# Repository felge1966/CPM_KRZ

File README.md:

# CPM_KRZ
Extrakt aus dem Beitrag im Robotrontrechnik-Forum

(https://www.robotrontechnik.de/html/forum/thwb/showtopic.php?threadid=12101)

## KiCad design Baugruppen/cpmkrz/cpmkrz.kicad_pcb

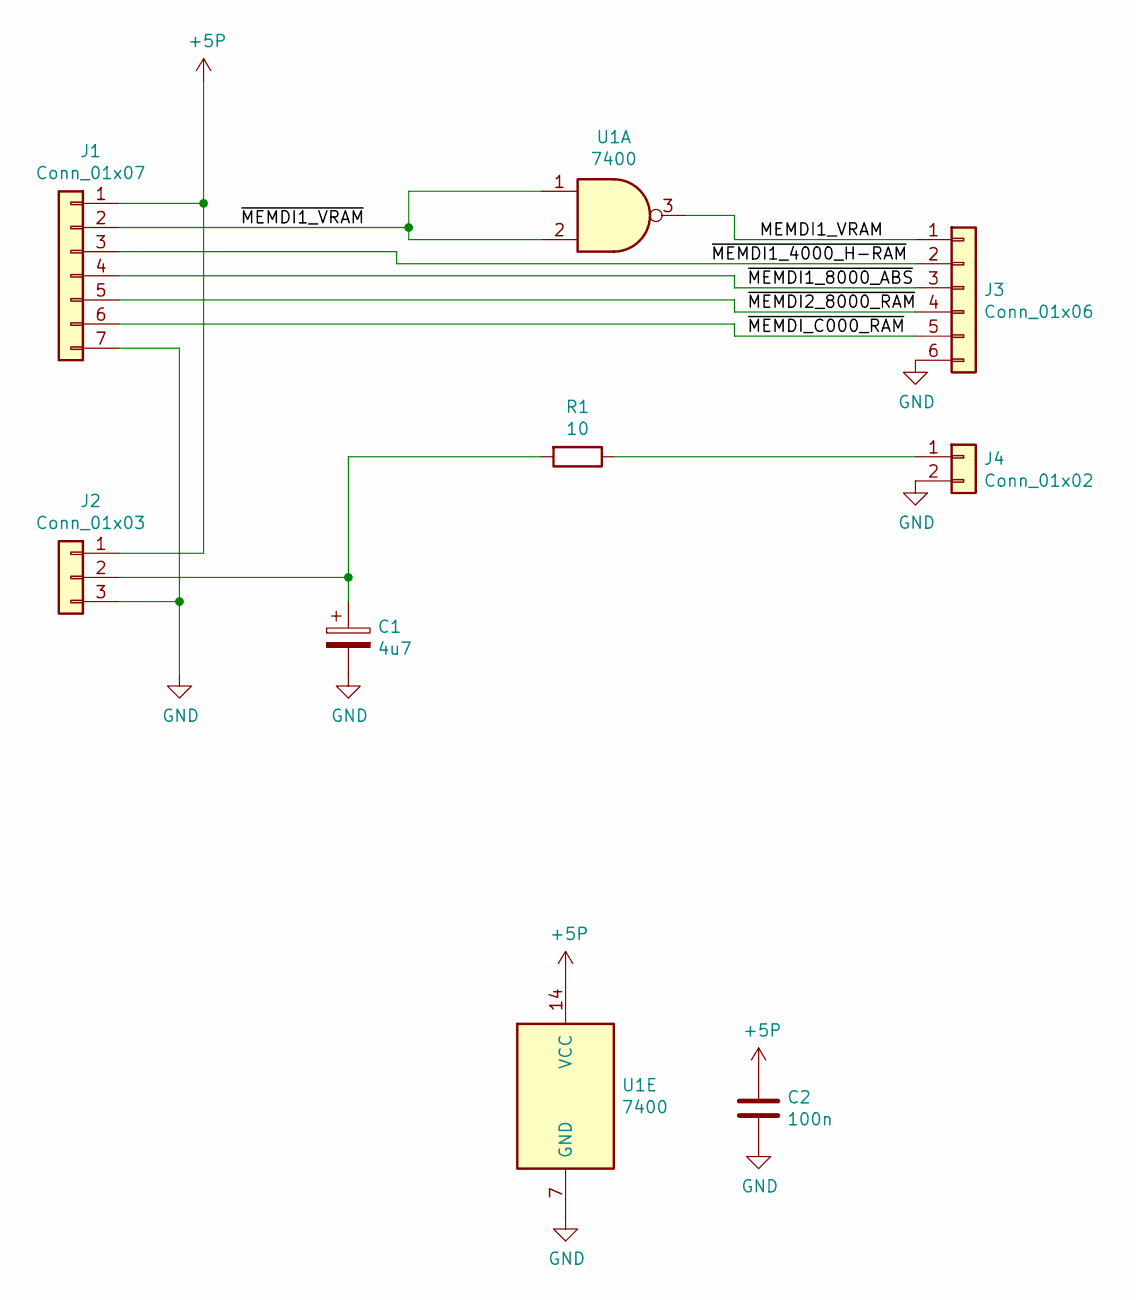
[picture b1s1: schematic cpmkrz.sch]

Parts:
C1: 4u7; CP_Radial_D6.3mm_P2.50mm
C2: 100n; C_Disc_D3.8mm_W2.6mm_P2.50mm
J1: Conn_01x07; PinHeader_1x07_P2.54mm_Horizontal
J2: Conn_01x03; PinHeader_1x03_P2.54mm_Horizontal
J3: Conn_01x06; PinHeader_1x06_P2.54mm_Horizontal
J4: Conn_01x02; PinHeader_1x02_P2.54mm_Horizontal
R1: 10; R_Axial_DIN0207_L6.3mm_D2.5mm_P10.16mm_Horizontal
U1: 7400; DIP-14_W7.62mm_LongPads

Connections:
+5P: C2.1, J1.1, J2.1, U1.14 (VCC)
/MEMDI1_VRAM: J3.1, U1.3
/~MEMDI1_4000_H-RAM: J1.3, J3.2
/~MEMDI1_8000_ABS: J1.4, J3.3
/~MEMDI1_VRAM: J1.2, U1.1, U1.2
/~MEMDI2_8000_RAM: J1.5, J3.4
/~MEMDI_C000_RAM: J1.6, J3.5
GND: C1.2, C2.2, J1.7, J2.3, J3.6, J4.2, U1.7 (GND)
unnamed: C1.1, J2.2, R1.2
unnamed: J4.1, R1.1

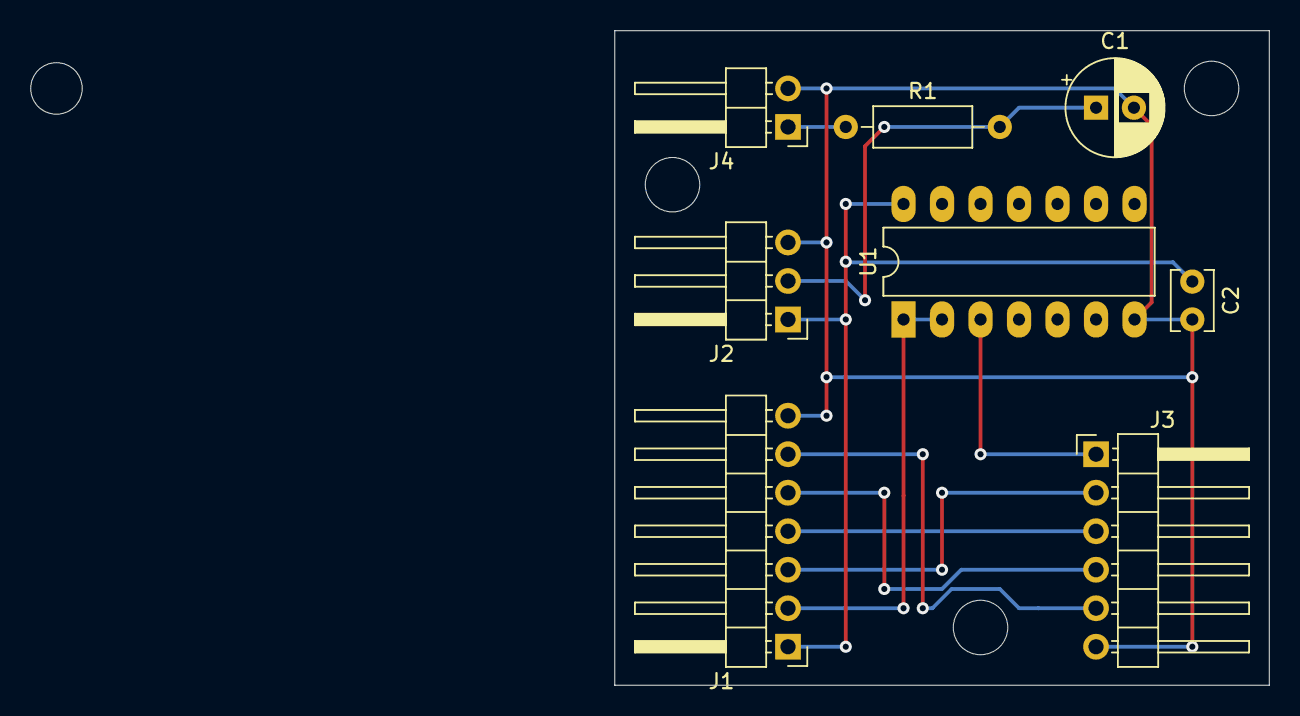
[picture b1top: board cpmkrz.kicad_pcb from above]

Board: 2 copper layers, 81.7 x 43.2 mm, 8 parts (0 on the bottom side), 10 nets.

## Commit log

2023-11-08 Create aufbau
2023-11-08 Rename aufbau to aufbau.md
2023-11-08 Rename assemblieren.md to assemblieren.doc
2023-11-08 Rename Konfig.md to Konfig.doc
